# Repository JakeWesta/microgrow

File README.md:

# Micro-Grow

- Flutter app demo video: https://www.youtube.com/watch?v=zIg6AqKC-sg

## Implemented Features:
### Pre-Alpha Build:
- **MQTT Connection** - Set up two-way communication between the ESP32 and the mobile app by using the MQTT protocol and EMQX broker.
- **Data Management** - Handle the storing of data by using a Hive database, which stores the watering cycle for each microgreen type.
- **Real-Time Sensor Data** - Configured ESP32 to poll readings from DHT11 temperature sensor and publishes the data every 5 seconds to the MQTT topic `microgrow/<habitatID>/sensor`.
- **User Interface** - Developed a Flutter app using Dart to allow the user to initialize and manage their MicroGrow habitat. Clicking on the habitat will display the real-time sensor data from the DHT11 on the app interface.

### Design Prototype:
- **Expanded Sensor Data** - Updated ESP32 code to publish sensor data for temperature/humidity, water level, and light intensity to MQTT topics `microgrow/<habitatID>/temp, humidity, water, light`. Sensor data is visible on the LCD screen to allow the user to easily monitor environmental conditions without their mobile device.
- **Expanded User Interface** - Updated dashboard to displays multiple created habitats and implemented the option to add and remove them. Selecting a habitat will display the real-time sensor data readings sent from the ESP32 for temperature, humidity, water level, and light intensity. Implemented the 'fun area' for the user to interact with their plant character
- **Schedule-Based Automation** - ESP32 pumps water from the water reservoir to the watering tray based on the watering schedule information sent during `microgrow/init`.
- **Manual Override** - Added a method for the user to control the water pump, fans, and light intensity manually from within the app. This feature does not interfere with the schedule timing.
- **Hardware** - Determined pin assignments for each electrical component. Connected ESP32, sensors, pump, lights, and LCD screen on a breadboard to test the functionality of each system. Designed CAD models to 3D-print the chassis and parts for the MicroGrow unit.

## Future Improvements:
- Include misting pump to regulate humidity within the habitat
- Create pixelated character sprites to display on the LCD screen
- Expand the 'fun area' in the mobile app to include customization features and scripted interaction between characters

## How to Use:

### Requirements:
- Flutter SDK
- Dart
- VS Code
- Arduino IDE
- Hive (for database)
- EMQX MQTT broker

### To setup the mobile application:
1. Ensure the required software is installed and install the necessary dependencies
2. Launch the mobile application:
   - Open VS Code and clone the repository
   - If prompted on VS Code, install the Flutter SDK and add to path if missing.
   - Install Flutter and Dart VS Code exstentions
   - Navigate to the app directory with `cd microgrow/app`
   - Fetch packages with `flutter pub get`
   - Connect to a 2.4 GHz WiFi network, such as a mobile hotspot
   - Start the application with `flutter run -d windows`
3. Flash the ESP32 firmware:
   - Open `main.ino` from the `ESP32 Firmware` directory in the Arduino IDE
   - Connect the ESP32 to a USB port on your computer
   - Follow the tutorial for the IDE to recognize the board: https://randomnerdtutorials.com/installing-the-esp32-board-in-arduino-ide-windows-instructions/
   - In Arduino IDE, select the correct configuration:
     - Board: ESP32 Dev Module
     - Port: auto-detected when plugging in
4. You may need to install the following packages. Easiest way is to go to the library manager tab on the left and search:
   - **PubSubClient** by Nick O'Leary
   - **DHT20** by Rob Tilaart
   - **ArduinoJson** by Benoit Blanchon
   - **Adafruit GFX Library** by Adafruit
   - **Adafruit ST7735 and ST7789 Library** by Adafruit
   - **FastLED** by Daniel Garcia
6. At the top of the code, assign the corresponding network information to the variables `ssid` and `password`
7. Press Upload and wait for flashing to complete

## Known Bugs:
- If sensor is unplugged, it displays garbage values. We don't handle that issue, as it displays more than 7 digits when disconnected from ESP32.
- If there is a disconnect from MQTT, we don't test for reconnection.
- Sometimes the ESP32 flashing will fail if its GPIO pins are connected to external peripherals/sensors. Remove the ESP32 from the breadboard before flashing to resolve this.
- Pump and fan will sometimes stop working during regular use.
- The current setup for the init sequence sends a JSON that is too large for the ESP32 to parse. This means that light scheduling is currently not being sent, as it had to be trimmed for the JSON to fit.

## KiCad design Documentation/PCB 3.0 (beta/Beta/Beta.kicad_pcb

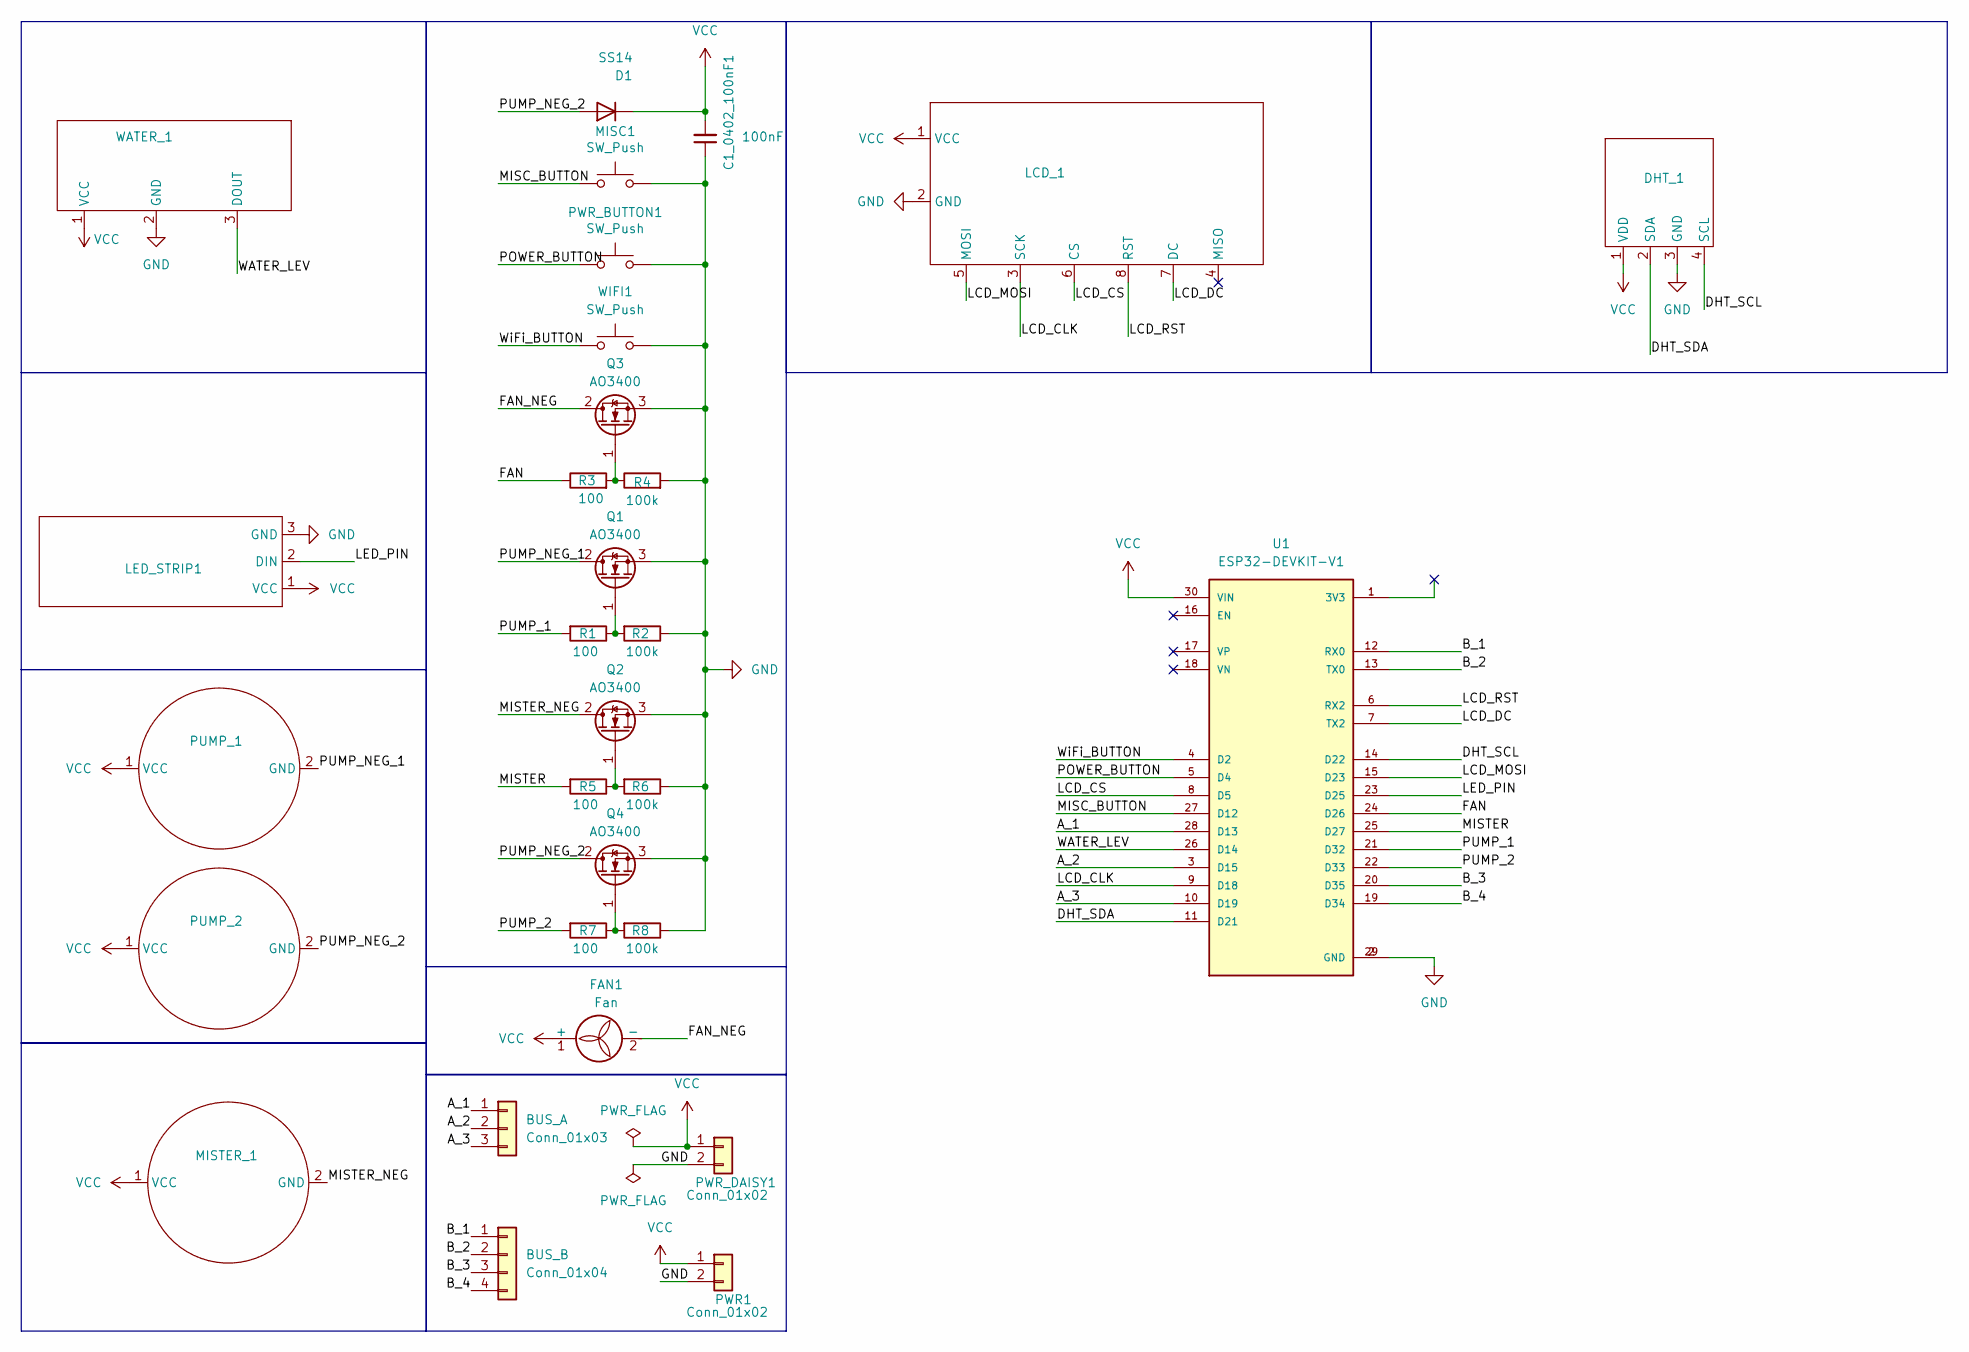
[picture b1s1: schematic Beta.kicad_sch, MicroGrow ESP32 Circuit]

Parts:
BUS_A: Conn_01x03; PinHeader_1x03_P1.00mm_Vertical
BUS_B: Conn_01x04; PinHeader_1x04_P1.00mm_Vertical
C1_0402_100nF1: 100nF; C_0402_1005Metric
D1: SS14; D_SOD-123
DHT_1: JST_PH_B4B-PH-K_1x04_P2.00mm_Vertical
FAN1: Fan; JST_PH_B2B-PH-K_1x02_P2.00mm_Vertical
LCD_1: 1x08(2 and 6) vertical JST PH
LED_STRIP1: JST_PH_B3B-PH-K_1x03_P2.00mm_Vertical
MISC1: SW_Push; JST_PH_B2B-PH-K_1x02_P2.00mm_Vertical
MISTER_1: JST_PH_B2B-PH-K_1x02_P2.00mm_Vertical
PUMP_1, PUMP_2: JST_PH_B2B-PH-K_1x02_P2.00mm_Vertical
PWR1: Conn_01x02; JST_VH_B2P-VH_1x02_P3.96mm_Vertical
PWR_BUTTON1: SW_Push; JST_PH_B2B-PH-K_1x02_P2.00mm_Vertical
PWR_DAISY1: Conn_01x02; JST_VH_B2P-VH_1x02_P3.96mm_Vertical
Q1, Q2, Q3, Q4: AO3400; SOT-23
R1, R3, R5, R7: 100; R_0402_1005Metric
R2, R4, R6, R8: 100k; R_0402_1005Metric
U1: ESP32-DEVKIT-V1; ESP32-C3-DevKitM-1; PARTREV N/A
WATER_1: JST_PH_B3B-PH-K_1x03_P2.00mm_Vertical
WIFI1: SW_Push; JST_PH_B2B-PH-K_1x02_P2.00mm_Vertical

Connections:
/A_1: BUS_A.1, U1.28 (D13); also elsewhere on the board
/A_2: BUS_A.2, U1.3 (D15); also elsewhere on the board
/A_3: BUS_A.3, U1.10 (D19); also elsewhere on the board
/B_1: BUS_B.1, U1.12 (RX0); also elsewhere on the board
/B_2: BUS_B.2, U1.13 (TX0); also elsewhere on the board
/B_3: BUS_B.3, U1.20 (D35); also elsewhere on the board
/B_4: BUS_B.4, U1.19 (D34); also elsewhere on the board
/DHT_SCL: DHT_1.4 (SCL), U1.14 (D22)
/DHT_SDA: DHT_1.2 (SDA), U1.11 (D21)
/FAN: R3.1, U1.24 (D26)
/FAN_NEG: FAN1.2 (-), Q3.2 (D)
/LCD_CLK: LCD_1.3 (SCK), U1.9 (D18)
/LCD_CS: LCD_1.6 (CS), U1.8 (D5)
/LCD_DC: LCD_1.7 (DC), U1.7 (TX2)
/LCD_MOSI: LCD_1.5 (MOSI), U1.15 (D23)
/LCD_RST: LCD_1.8 (RST), U1.6 (RX2)
/LED_PIN: LED_STRIP1.2 (DIN), U1.23 (D25)
/MISC_BUTTON: MISC1.1, U1.27 (D12)
/MISTER: R5.2, U1.25 (D27)
/MISTER_NEG: MISTER_1.2 (GND), Q2.2 (D)
/POWER_BUTTON: PWR_BUTTON1.1, U1.5 (D4)
/PUMP_1: R1.2, U1.21 (D32)
/PUMP_2: R7.2, U1.22 (D33)
/PUMP_NEG_1: PUMP_1.2 (GND), Q1.2 (D)
/PUMP_NEG_2: D1.2 (A), PUMP_2.2 (GND), Q4.2 (D)
/WATER_LEV: U1.26 (D14), WATER_1.3 (DOUT)
/WiFi_BUTTON: U1.4 (D2), WIFI1.1
GND: C1_0402_100nF1.1, DHT_1.3 (GND), LCD_1.2 (GND), LED_STRIP1.3 (GND), MISC1.2, PWR1.2, PWR_BUTTON1.2, PWR_DAISY1.2, Q1.3 (S), Q2.3 (S), Q3.3 (S), Q4.3 (S), R2.1, R4.2, R6.1, R8.1, U1.2 (GND), U1.29 (GND), WATER_1.2 (GND), WIFI1.2
unnamed: Q1.1 (G), R1.1, R2.2
unnamed: Q2.1 (G), R5.1, R6.2
unnamed: Q3.1 (G), R3.2, R4.1
unnamed: Q4.1 (G), R7.1, R8.2
VCC: C1_0402_100nF1.2, D1.1 (K), DHT_1.1 (VDD), FAN1.1 (+), LCD_1.1 (VCC), LED_STRIP1.1 (VCC), MISTER_1.1 (VCC), PUMP_1.1 (VCC), PUMP_2.1 (VCC), PWR1.1, PWR_DAISY1.1, U1.30 (VIN), WATER_1.1 (VCC)

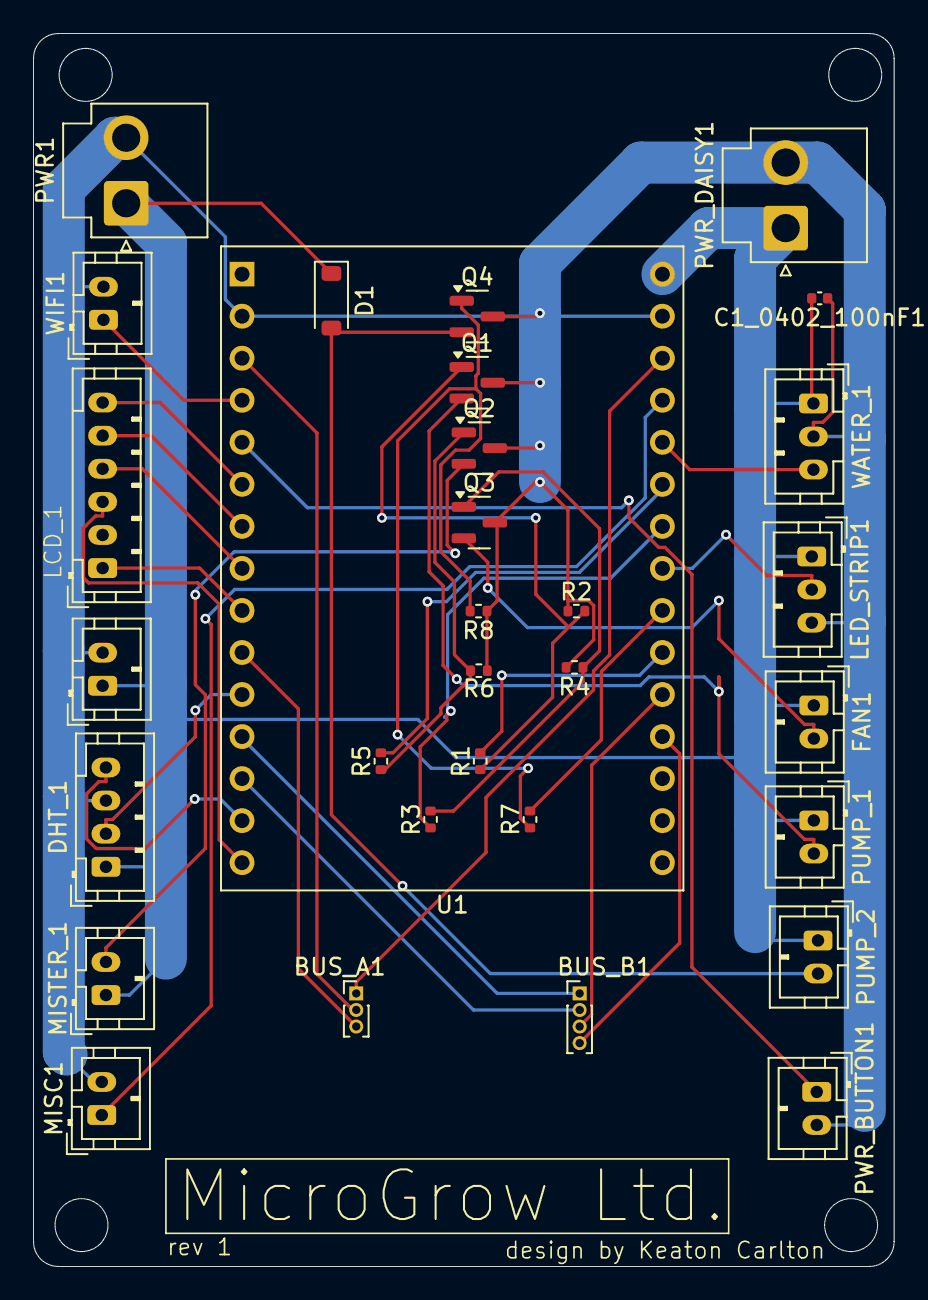
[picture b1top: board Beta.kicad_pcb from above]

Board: 2 copper layers, 52.0 x 74.5 mm, 30 parts (0 on the bottom side), 33 nets.

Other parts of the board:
BUS_A1: Conn_01x03; PinHeader_1x03_P1.00mm_Vertical
BUS_B1: Conn_01x04; PinHeader_1x04_P1.00mm_Vertical

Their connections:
/A_1: BUS_A1.1; also elsewhere on the board
/A_2: BUS_A1.2; also elsewhere on the board
/A_3: BUS_A1.3; also elsewhere on the board
/B_1: BUS_B1.1; also elsewhere on the board
/B_2: BUS_B1.2; also elsewhere on the board
/B_3: BUS_B1.3; also elsewhere on the board
/B_4: BUS_B1.4; also elsewhere on the board

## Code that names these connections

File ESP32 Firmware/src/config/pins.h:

#pragma once

// Button for WiFi reset
#define PIN_WIFI_BUTTON 12
#define PIN_POWER_BUTTON 4

// LED Strip
#define PIN_LED_STRIP 25
#define NUM_LEDS 256

// Actuators
#define PIN_WATER_PUMP1 32
#define PIN_WATER_PUMP2 33
#define PIN_FAN 26
#define PIN_MISTER 27

// Sensors
#define PIN_WATER_LEVEL 14

// TFT Display
#define TFT_CS 5
#define TFT_DC 17
#define TFT_RST 16
#define TFT_MOSI 23
#define TFT_SCLK 18
#define TFT_MISO 19

// SD Card
#define SD_CS 2

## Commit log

2025-10-13 Update links.txt
    Include link to Work Log spreadsheet for Matthew Juranek
2025-10-13 Rename links.txt to Individual_Logs.txt
2025-10-16 Create Contributions
2025-10-17 Delete Documentation directory
    Error in naming convention
2025-10-18 Delete App directory
    issue with flutter app creation
2025-10-18 initial flutter app created in app folder.
2025-10-18 very base level foudnation for MQTT implementation
2025-10-22 Creates MQTT functionality, demonstrates ADC, PWM
    Useful for demonstration of key features
2025-10-23 Set up MQTT connection for Flutter
2025-10-25 Fixed merge for main, going to switch to new branch to develop
2025-10-26 New file structure. Beginning to make changes to main.dart based on tutorial, move UI to home_screen.dart, and state to app_state.dart
2025-10-26 commented out widget_test.dart for now.
2025-10-26 initial app state with a Habitat class to keep track of each Micro-Grow habitat
2025-10-26 basic ui for home_screen.dart
2025-10-26 Remade app_state and added database.dart to keep track of persistent data locally with Hive
2025-10-26 Realized I needed CHangeNotifier and a true app state if I wanted to update UI reactively. Added back, moved habitat class to habitat_obj.dart.
2025-10-26 home screen done (i hope) with navigation in place, just need to do other 2 ui screens
2025-10-26 add habitat screen mostly done, has validation for input entries before trying to save to database.
2025-10-26 revamped MQTT to be its own class. Made connect() its own function. added and tested a setupHabitat to init an ESP32. added sensorSubscribe to tap into ESP32 sensor topic.
2025-10-26 sensor subscribe didn't get added with last commit
2025-10-26 added Mqtt setupHabitat call after habitat is made. Works! hardcoded habitatId so I can test easier for now
2025-10-26 sensor data viewing screen with MQTT functionality to subscribe to selected habitat id sensor topic
2025-10-26 dependency file updates and main.dart update
2025-10-27 Refactor MQTT and sensor integration
    Updated WiFi and MQTT connection details, added DHT sensor support, and improved message handling.
2025-10-27 Update README with project details and future plans
    Expanded README with prototype details, features, bugs, and future improvements.
2025-11-04 Got MQTT working as a non-websocket based connection. Now works for Windows native, and should for mobile app. Also VS code fixed some other nonused imports.
2025-11-04 added debug button that clears habitats. Also made it so that multiple habitats can be shown.
2025-11-13 made it possbile to delete habitats on app state side
2025-11-13 added button to delete habitats on UI side
2025-11-15 There's a decent amount of small changes kinda lost track oops. Most recent is getting current time to send to esp32 for scheduling
2025-11-15 Refactored how the database is structured and how MQTT data is sent for scheduling purposes
2025-11-15 Got manual override screen up and running, checked with MQTT broker and its sending what we need.
2025-11-15 Gorgeous UI changes. God its so pretty
2025-11-15 Sensor screen UI update
2025-11-15 Added a true main screen that has a bottom nav bar to go between habitat home/manager and the future tomagachi/garden area.
2025-11-15 Compile ESP32 code to updated main.ino, update MQTT topic paths
2025-11-16 Added all STLs
2025-11-16 Add files via upload
    added wifi pushbutton
2025-11-17 Made the Garden section, which for now is the habitat icons jumping around rythmically.
2025-11-17 Rename Individual_Logs.txt to Contributions.txt
2025-11-17 Revise README for improved clarity and organization
    Updated README to enhance clarity and structure, added sections for components, implemented features, usage instructions, and known bugs.
2025-11-17 STL file and screenshots of 3D model
2025-11-17 Update README to specify pre-alpha and design prototype features
    Updated README to reflect pre-alpha build features and design prototype details.
2025-11-17 had to remove light schedule to fix bug
2025-11-17 demo
2025-11-17 brhian and cj code combined
2025-11-17 Didnt realize there was small bug where delete would occur over MQTT before confirming
2025-11-17 made small MQTT init fix to break up init messages so ESP32 can parse easily
2025-11-17 Made it so that the lights can be set to a certain color over MQTT
2025-11-17 led override any color
2025-11-18 Publish led state
2025-11-18 light control for LED override
2025-11-18 Improved sensor reading screen
2025-11-18 Implemented a party time. So cool.
2025-11-18 Had to refactor MQTT and Database to now use Seconds instread of Miliseconds for scheduling
2025-11-18 Fixed Water level sensor parsing
2025-11-18 Small changes
2025-11-18 edited pins and fixed stuff
2025-11-18 fixed humidity
    made DHT20 read only once. Fixes the routine of getting temp + humidity. Required a file scope "status" variable for DHT20 for minimal changes to structure.
2025-11-18 Added platformIO IDE functionality to ESP32 Firmware
    Easiest way to use this is to install the platformIO extension on VS code and build/upload to the DevKit
2026-01-25 1/24 contribution
2026-01-27 keaton work log 1/27
2026-01-29 CJ work log
2026-01-29 Add control logic for humidifier module. Add switch case in mqtt.cpp for manual override.
2026-01-30 new approach (OOP)
2026-01-30 1/30
2026-01-31 Create PCB folder
2026-01-31 Uploaded Alpha Build PCB Schematic, Layout
2026-01-31 Update Keaton Carlton
2026-01-31 Sorry for a massive dump instead of smaller commits of files but I change them all so much because I mess up that I thought I'd just send them all when done. MAde water reservoir from ground up, took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
2026-01-31 Added a field to 'Add a Habitat' screen that allows for a unique ID to be put in. This fixes the issue where every habitat hypothetically made would share a topic, and now can be differentiated. Also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
2026-02-04 Made it so that the mister now has manual override on the app side.
2026-02-04 add mister override
2026-02-04 fixed topic names
2026-02-04 get rid of habitatId
2026-02-05 DHT sensor fixed and got rid of old Arduino stuff. Also improved scheduler and made esp actaully used the saved configuration
2026-02-05 seems good
2026-02-07 added pcb updates
2026-02-07 updated schematic dates/details
2026-02-09 uploaded revision of pcb
2026-02-09 work logs wk of 2/1/26
2026-02-11 Tried to implement coin system for harvesting microgreens. Works, but not sure I like the current architecture for expanding. Gonna plan it out more then continue
2026-02-12 get rid of .vscode
2026-02-12 work log CJ
2026-02-12 Realized there was no tolerance for many components, and the way I made everything made that annoying to fix. Also had to change the base for the new LCD screen size, which I also made extremely diff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
2026-02-12 fix scheduler
2026-02-12 pause and resume water
2026-02-12 change displays
2026-02-12 Front Door
    Forgot to commit front door chagnes
2026-02-12 Attempt 2 at door changes
2026-02-12 no more backlight
2026-02-12 work log
2026-02-14 pcb revision
2026-02-18 save a reading every hour to nvs
2026-02-18 change interval to macro
2026-02-18 clear data after refresh
2026-02-19 Preliminary past sensor readings. I need to add functionality to save it to Hive database but it already took longer than expected so will do that later.
2026-02-20 Added functionality so that sensor data is saved and displayed properly
2026-02-20 added a feature that allows for a graphical representation of temp and humidity from past sensor logs from moment of habitat creation
2026-02-20 made it so that the user gets a notification when water reservoir needs to be refilled
2026-02-21 Replace with correct files
2026-02-21 Remodeled the garden section, now called greenhouse section. Made it so that habitats, upon creation, are entered into a 2x3 grid that represents the physical configuration (will make it customizable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
2026-02-24 Made it so that growht is tracked incrementally now. also made it so that game reflects this with cute pngs
2026-02-24 we've been grinding for like 5 hours ive forgotten what ive added sorry
2026-02-24 formatted date time to look better
2026-02-24 lcd things
2026-02-24 change reading count
2026-02-24 growth configuration
2026-02-24 schedule fix
2026-02-25 Implement logic for LED feedback
2026-02-26 Add automation function to drive LED feedback
2026-02-28 Set up files for Firebase integration
2026-03-05 Update config for Firebase notifications
2026-03-13 Fix conflict with pump manual override and water schedule
2026-03-25 Added blackout periods as a possible plant feature. Made it so that it is kept tracked such as reservoir or harvest ready. Also, made it so that it is published to MQTT when over so that ESP32 can re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
2026-03-25 Made blackout MQTT message be retained just in case habitat is off
2026-03-25 Made blackout time effect progress bar
2026-03-26 Configure setup for sending local push notifications to Android device
2026-03-27 overhauled the reward system and the game screen. Got some pngs of decorations as well as a room background. Made it so that the player is rewarded coins daily per habitat, as well as when harvesting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
2026-04-02 Made it so that blackout notification is rememered and only sent once. Made it so taht toggles are stored persistently.
2026-04-13 Massive overhaul of game section/greenhouse. New images were generated, adding 5 new plants able to be chosen when creating a habitat. Greenhouse section has a proper background now. The user can als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
2026-04-15 send light data
2026-04-15 refactored approach to persistence manager and implemented water pump pulse
2026-04-16 Add push notifs to test
2026-04-16 fix include error
2026-04-16 fix display
2026-04-17 shutdown and fix buttons. Also change includes to use <> instead of ""
2026-04-19 button functionality compelete. Display updated
2026-04-21 its the final countdownnn
2026-04-21 start on custom images
2026-04-21 This jake west. so many changes. 12 hours of work. god.
2026-04-21 dr gomes recommendation
2026-04-28 make MQTT singleton more idiomatic
2026-04-28 readings valid uncommented
